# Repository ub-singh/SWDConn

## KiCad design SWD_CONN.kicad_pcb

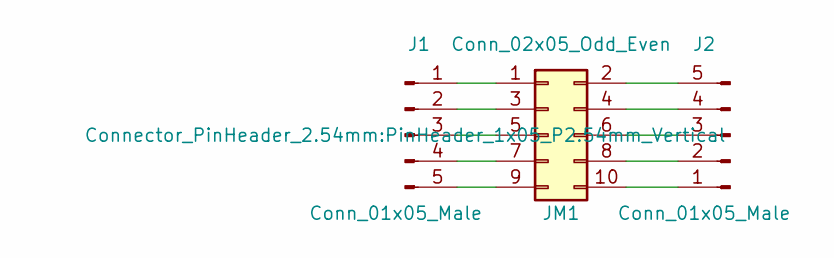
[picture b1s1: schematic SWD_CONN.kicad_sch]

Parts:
J1, J2: Conn_01x05_Male; PinHeader_1x05_P2.54mm_Vertical
JM1: Conn_02x05_Odd_Even; PinHeader_2x05_P1.27mm_Vertical_SMD

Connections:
unnamed: J1.1, JM1.1
unnamed: J1.2, JM1.3
unnamed: J1.3, JM1.5
unnamed: J1.4, JM1.7
unnamed: J1.5, JM1.9
unnamed: J2.1, JM1.10
unnamed: J2.2, JM1.8
unnamed: J2.3, JM1.6
unnamed: J2.4, JM1.4
unnamed: J2.5, JM1.2

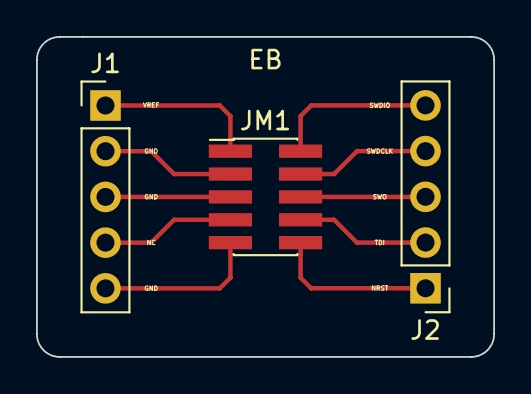
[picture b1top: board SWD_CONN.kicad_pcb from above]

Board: 2 copper layers, 25.4 x 17.8 mm, 3 parts (0 on the bottom side), 10 nets.

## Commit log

2022-08-09 Kicad files for SWD/JTAG connector
